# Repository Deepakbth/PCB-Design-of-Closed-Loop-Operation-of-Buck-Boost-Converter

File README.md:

# PCB-Design-of-Closed-Loop-Operation-of-Buck-Boost-Converter

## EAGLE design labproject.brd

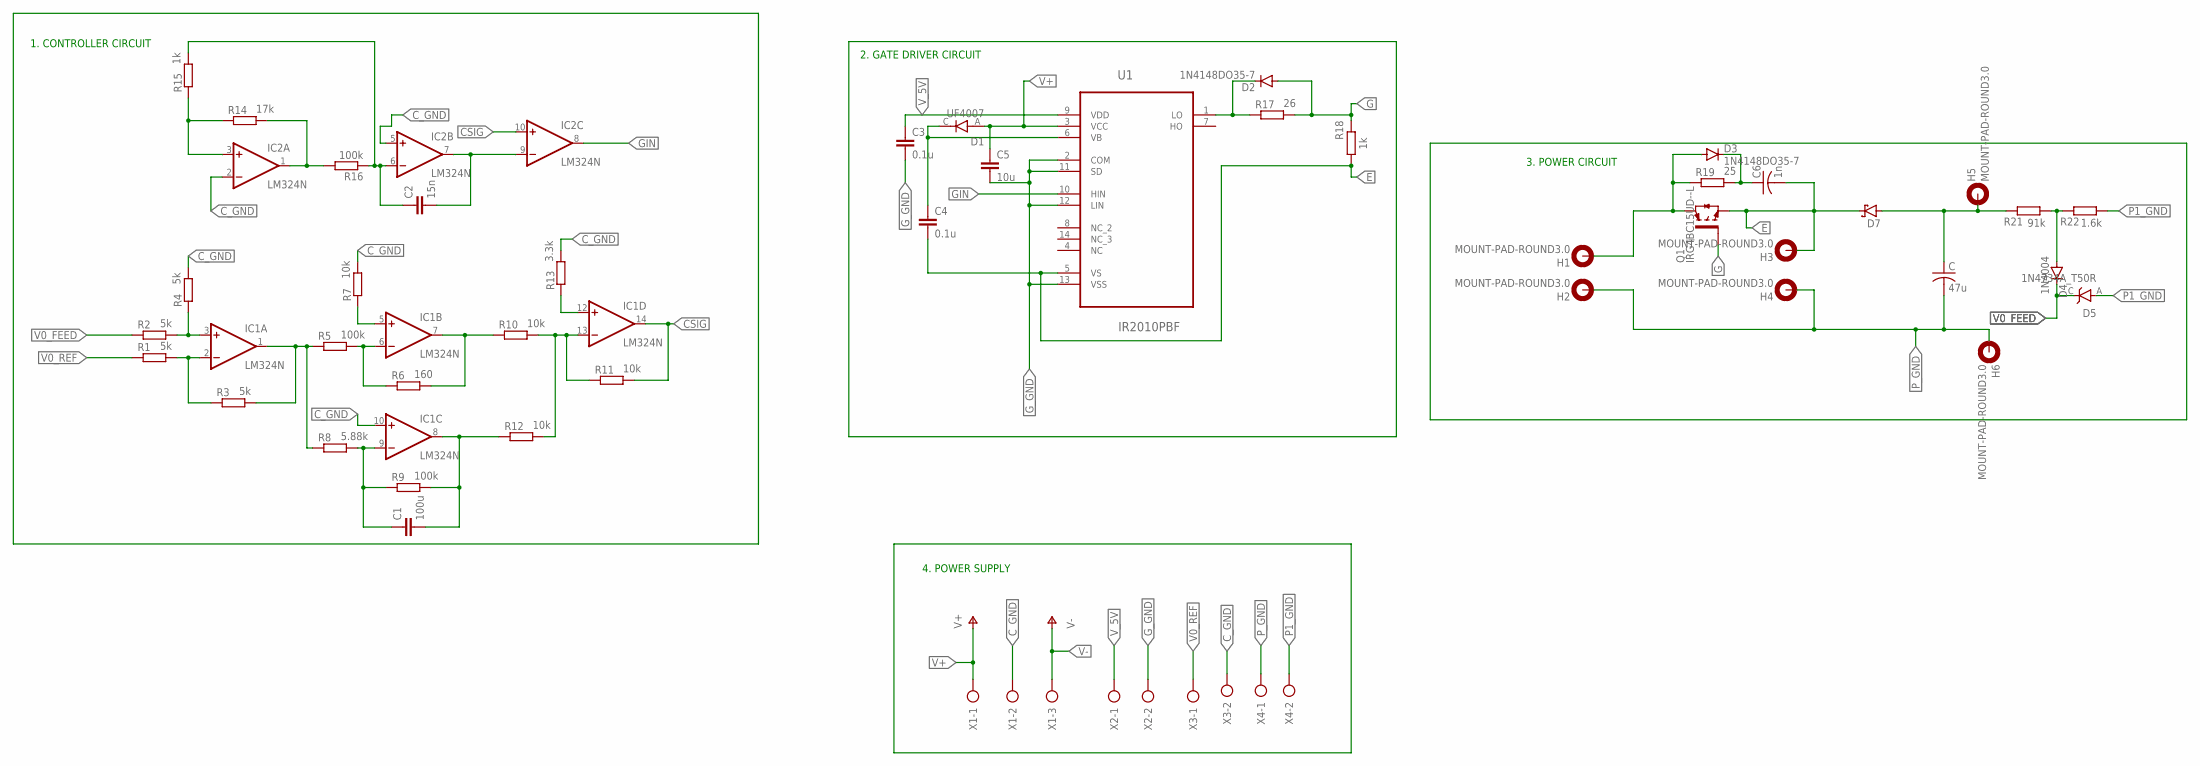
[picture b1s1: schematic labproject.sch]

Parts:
C: 47u; C075-032X103
C1: 100u; C025-024X044
C2: 15n; C025-024X044
C3, C4: 0.1u; C025-024X044
C5: 10u; C025-024X044
C6: 1n; C075-032X103
D1: UF4007; DIOAD1055W87L533D272
D2, D3: 1N4148DO35-7; DO35-7
D4: 1N4004; DO41-10
D5: 1N4734A_T50R; DIOAD1070W78L463D238P
D7: SCHOTTKY-DIODEDO201T15; DO201T15
H1, H2, H3, H4, H5, H6: MOUNT-PAD-ROUND3.0; 3,0-PAD
IC1, IC2: LM324N; DIL14
Q1: IRG4BC15UD--L; TO262-V
R1, R2, R3, R4: 5k; 0204/7
R5, R9, R16: 100k; 0204/7
R6: 160; 0204/7
R7, R10, R11, R12: 10k; 0204/7
R8: 5.88k; 0204/7
R13: 3.3k; 0204/7
R14: 17k; 0204/7
R15, R18: 1k; 0204/7
R17: 26; 0204/7
R19: 25; 0204/7
R21: 91k; 0204/7
R22: 1.6k; 0204/7
U1: IR2010PBF; DIP254P762X533-14
X1: AK300/3
X2, X3, X4: AK300/2

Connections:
CSIG: IC1.14 (OUT), IC2.10 (+IN), R11.2
C_GND: IC1.10 (+IN), IC2.2 (-IN), IC2.5 (+IN), R4.2, R7.2, R13.2, X1.2, X3.2
E: C4.2, C6.2, D7.C, H3.B3,0, Q1.3 (E), R18.2, U1.5 (VS)
G: D2.A, Q1.1 (G), R17.2, R18.1
GIN: IC2.8 (OUT), U1.10 (HIN)
G_GND: C3.2, C5.2, U1.2 (COM), U1.11 (SD), U1.12 (LIN), U1.13 (VSS), X2.2
unnamed: IC1.3 (+IN), R2.2, R4.1
unnamed: IC1.2 (-IN), R1.2, R3.1
unnamed: IC1.1 (OUT), R3.2, R5.1, R8.1
unnamed: IC1.6 (-IN), R5.2, R6.1
unnamed: IC1.5 (+IN), R7.1
unnamed: IC1.7 (OUT), R6.2, R10.1
unnamed: IC1.13 (-IN), R10.2, R11.1, R12.2
unnamed: C1.1, IC1.9 (-IN), R8.2, R9.1
unnamed: C1.2, IC1.8 (OUT), R9.2, R12.1
unnamed: IC1.12 (+IN), R13.1
unnamed: IC2.1 (OUT), R14.2, R16.2
unnamed: IC2.3 (+IN), R14.1, R15.1
unnamed: C2.1, IC2.6 (-IN), R15.2, R16.1
unnamed: C2.2, IC2.7 (OUT), IC2.9 (-IN)
unnamed: C4.1, D1.C (K), U1.6 (VB)
unnamed: D2.C, R17.1, U1.1 (LO)
unnamed: D3.A, H1.B3,0, Q1.2 (C), R19.1
unnamed: C6.1, D3.C, R19.2
unnamed: C.1, D7.A, H5.B3,0, R21.2
unnamed: D4.A, R21.1, R22.2
P1_GND: D5.A, R22.1, X4.2
P_GND: C.2, H2.B3,0, H4.B3,0, H6.B3,0, X4.1
V0_FEED: D4.C, D5.C, R2.1
V0_REF: R1.1, X3.1
V+: C5.1, D1.A, IC1.4 (V+), IC2.4 (V+), U1.3 (VCC), X1.1
V-: IC1.11 (V-), IC2.11 (V-), X1.3
V_5V: C3.1, U1.9 (VDD), X2.1

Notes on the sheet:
2. GATE DRIVER CIRCUIT
1. CONTROLLER CIRCUIT
4. POWER SUPPLY
3. POWER CIRCUIT

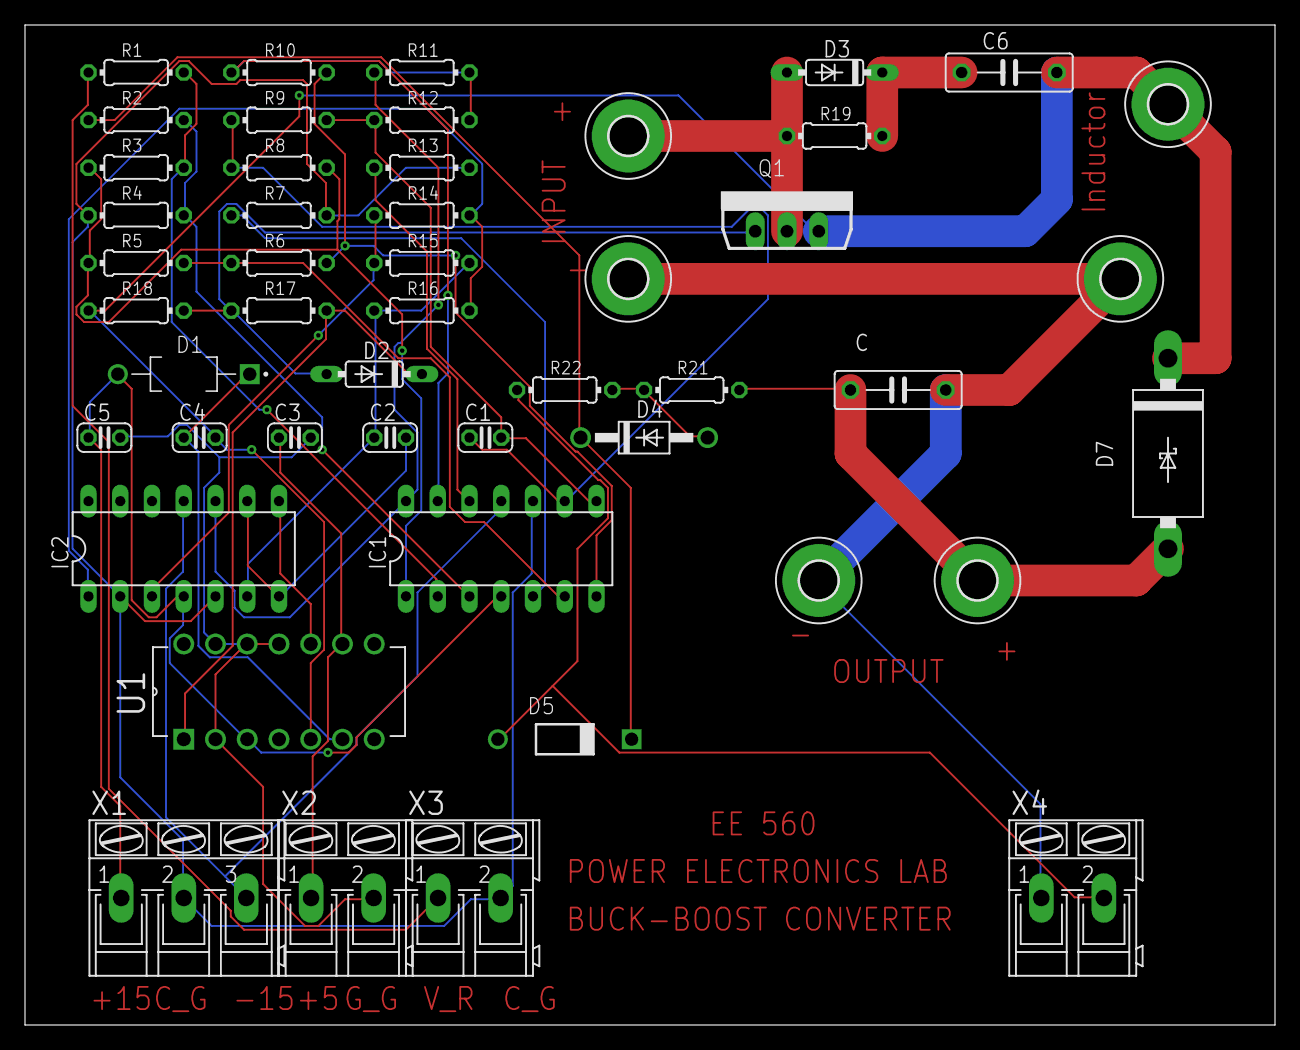
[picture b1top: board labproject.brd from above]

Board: 2 copper layers, 100.0 x 80.0 mm, 48 parts (0 on the bottom side), 33 nets.
